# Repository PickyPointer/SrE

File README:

SrE Readme
git remote add origin https://github.com/PickyPointer/SrE.git
git push origin master
git pull origin master

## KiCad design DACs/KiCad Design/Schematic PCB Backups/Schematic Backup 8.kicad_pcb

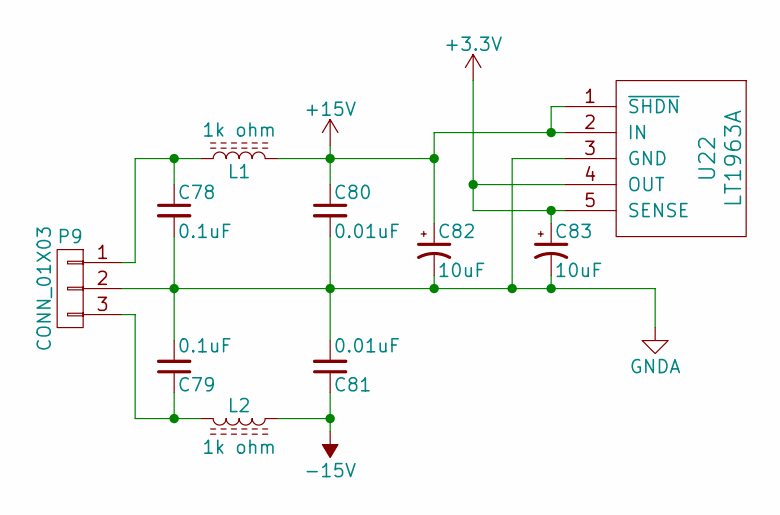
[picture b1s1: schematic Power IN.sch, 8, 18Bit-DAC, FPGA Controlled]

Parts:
C78, C79: 0.1uF; C_0805_HandSoldering
C80, C81: 0.01uF; C_0805_HandSoldering
C82, C83: 10uF; CP_Tantalum_Case-A_EIA-3216-18_Hand
L1, L2: 1k ohm; C_1812_HandSoldering
P9: CONN_01X03; PINHEAD1-3
U22: LT1963A; TO-220-5_Pentawatt_Multiwatt-5_Vertical_StaggeredType1

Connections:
+3V3: C83.1, U22.4 (OUT), U22.5 (SENSE); also elsewhere on the board
+15V: C80.1, C82.1, L1.2, U22.1 (~SHDN~), U22.2 (IN); also elsewhere on the board
-15V: C81.1, L2.2; also elsewhere on the board
GNDA: C78.2, C79.2, C80.2, C81.2, C82.2, C83.2, P9.2, U22.3 (GND); also elsewhere on the board
unnamed: C78.1, L1.1, P9.1
unnamed: C79.1, L2.1, P9.3

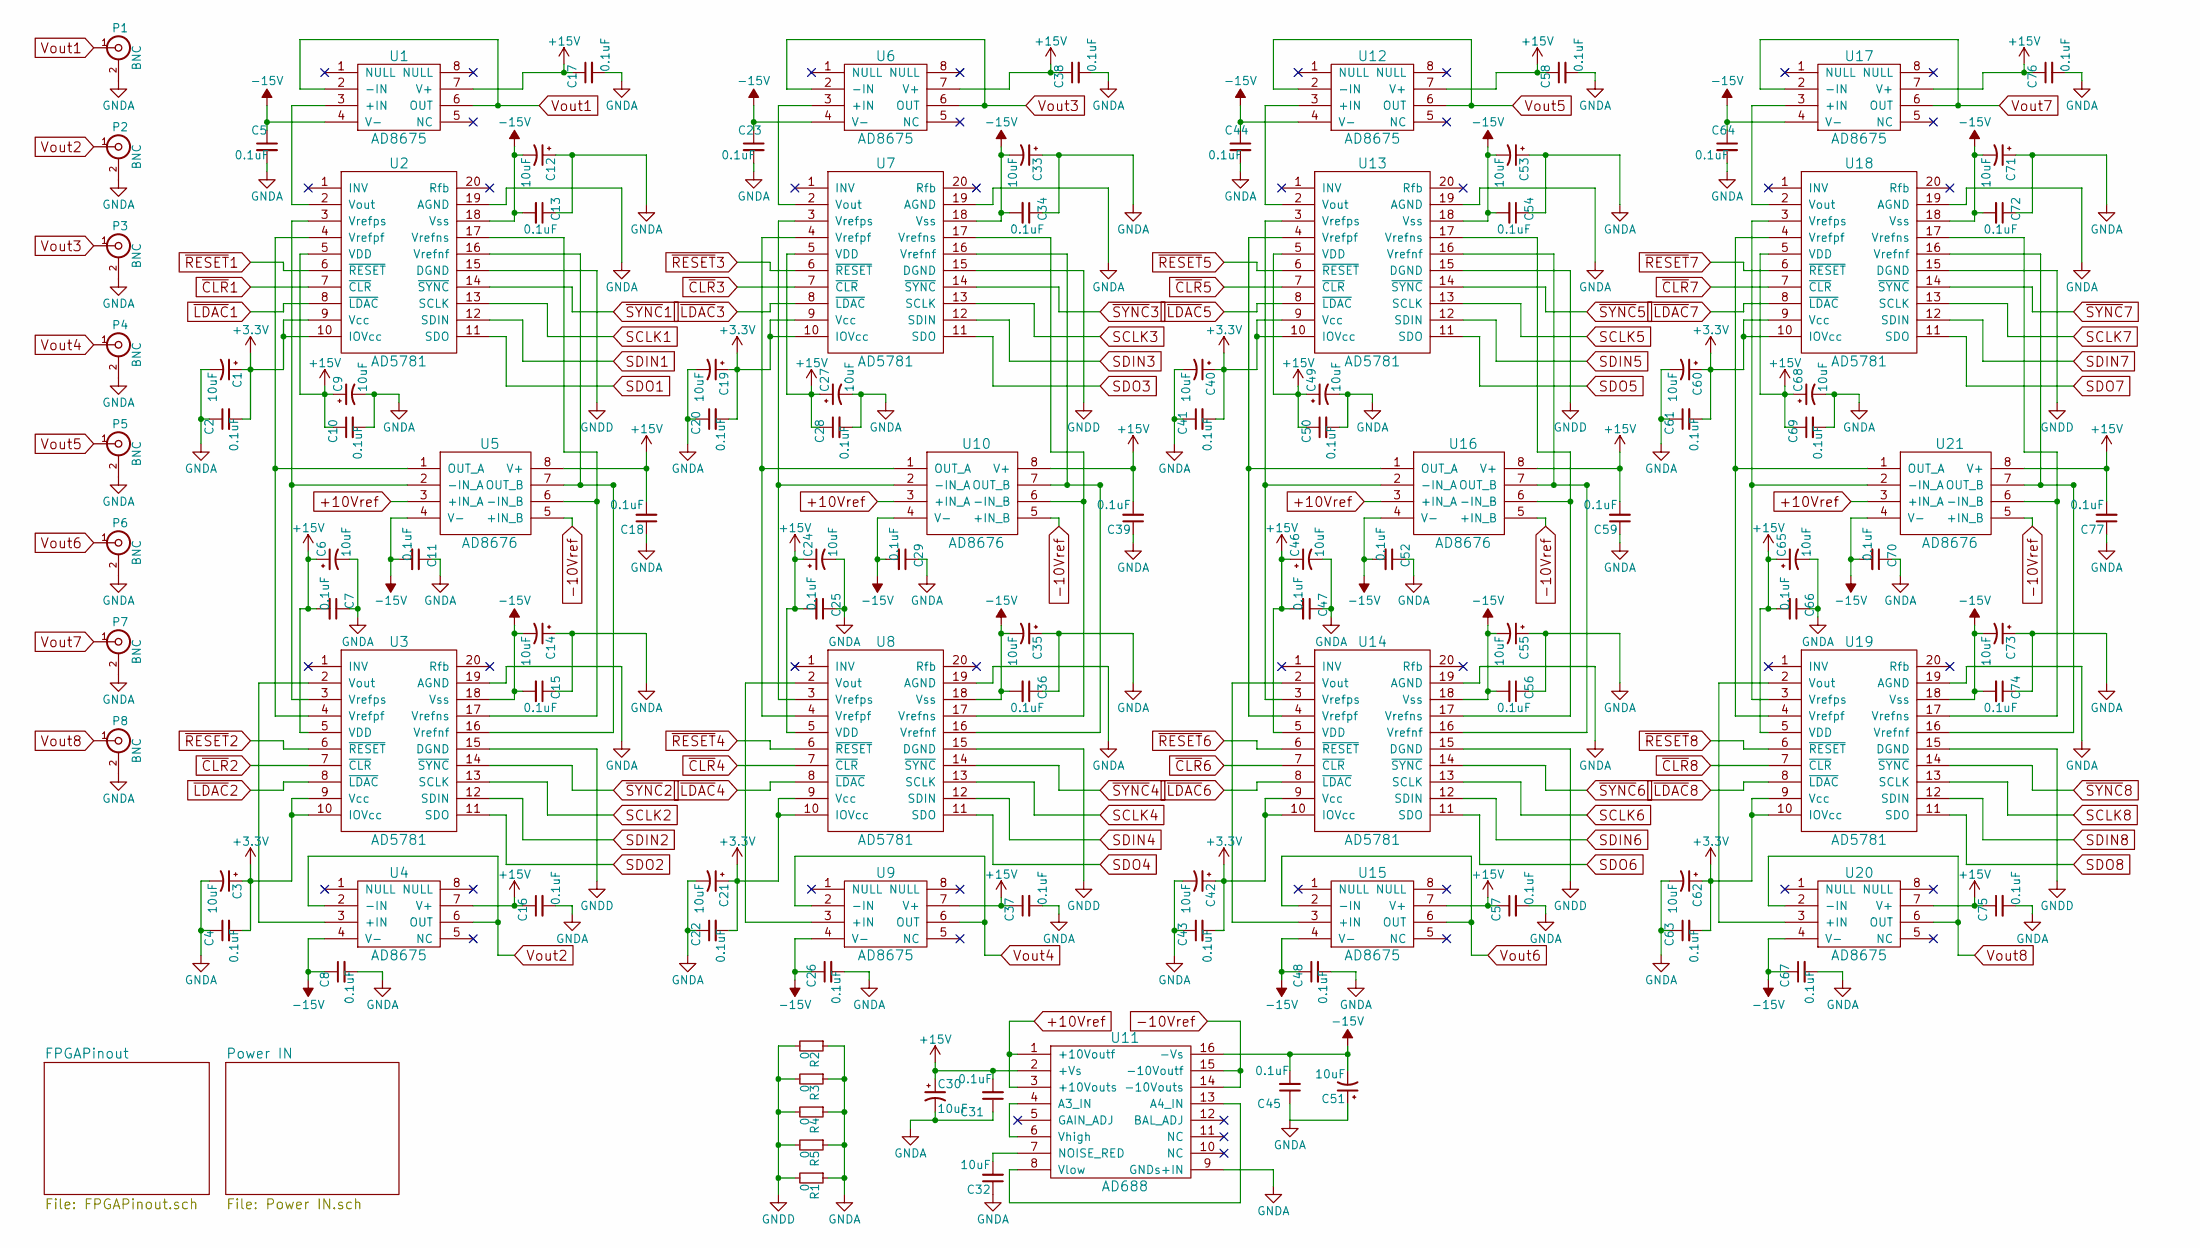
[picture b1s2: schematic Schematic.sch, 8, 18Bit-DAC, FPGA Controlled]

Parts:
C1, C3, C6, C9, C12, C14, C19, C21, C24, C27, C30, C33, C35, C40, C42, C46, C49, C51, C53, C55, C60, C62, C65, C68, C71, C73: 10uF; CP_Tantalum_Case-A_EIA-3216-18_Hand
C2, C4, C5, C7, C8, C10, C11, C13, C15, C16, C17, C18, C20, C22, C23, C25, C26, C28, C29, C31, C34, C36, C37, C38, C39, C41, C43, C44, C45, C47, C48, C50, C52, C54, C56, C57, C58, C59, C61, C63, C64, C66, C67, C69, C70, C72, C74, C75, C76, C77: 0.1uF; C_0805_HandSoldering
C32: 10uF; C_Disc_D3.4mm_W2.1mm_P2.50mm
P1, P2, P3, P4, P5, P6, P7, P8: BNC; BNC_Socket_TYCO-AMP_LargePads
R1, R2, R3, R4, R5: 0; R_0805_HandSoldering
U1, U4, U6, U9, U12, U15, U17, U20: AD8675; AD8675ARZ
U2, U3, U7, U8, U13, U14, U18, U19: AD5781; AD5781ARUZ
U5, U10, U16, U21: AD8676; AD8676ARZ
U11: AD688; AD688ARWZ

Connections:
+3V3: C1.1, C2.2, C3.1, C4.2, C19.1, C20.2, C21.1, C22.2, C40.1, C41.2, C42.1, C43.2, C60.1, C61.2, C62.1, C63.2, U2.9 (Vcc), U2.10 (IOVcc), U3.9 (Vcc), U3.10 (IOVcc), U7.9 (Vcc), U7.10 (IOVcc), U8.9 (Vcc), U8.10 (IOVcc), U13.9 (Vcc), U13.10 (IOVcc), U14.9 (Vcc), U14.10 (IOVcc), U18.9 (Vcc), U18.10 (IOVcc), U19.9 (Vcc), U19.10 (IOVcc); also elsewhere on the board
+10Vref: U5.3 (+IN_A), U10.3 (+IN_A), U11.1 (+10Voutf), U11.3 (+10Vouts), U16.3 (+IN_A), U21.3 (+IN_A)
+15V: C6.1, C7.2, C9.1, C10.1, C16.1, C17.1, C18.2, C24.1, C25.2, C27.1, C28.1, C30.1, C31.2, C37.1, C38.1, C39.2, C46.1, C47.2, C49.1, C50.1, C57.1, C58.1, C59.2, C65.1, C66.2, C68.1, C69.1, C75.1, C76.1, C77.2, U1.7 (V+), U2.5 (VDD), U3.5 (VDD), U4.7 (V+), U5.8 (V+), U6.7 (V+), U7.5 (VDD), U8.5 (VDD), U9.7 (V+), U10.8 (V+), U11.2 (+Vs), U12.7 (V+), U13.5 (VDD), U14.5 (VDD), U15.7 (V+), U16.8 (V+), U17.7 (V+), U18.5 (VDD), U19.5 (VDD), U20.7 (V+), U21.8 (V+); also elsewhere on the board
-10Vref: U5.5 (+IN_B), U10.5 (+IN_B), U11.14 (-10Vouts), U11.15 (-10Voutf), U16.5 (+IN_B), U21.5 (+IN_B)
-15V: C5.1, C8.1, C11.2, C12.2, C13.2, C14.2, C15.2, C23.1, C26.1, C29.2, C33.2, C34.2, C35.2, C36.2, C44.1, C45.2, C48.1, C51.2, C52.2, C53.2, C54.2, C55.2, C56.2, C64.1, C67.1, C70.2, C71.2, C72.2, C73.2, C74.2, U1.4 (V-), U2.18 (Vss), U3.18 (Vss), U4.4 (V-), U5.4 (V-), U6.4 (V-), U7.18 (Vss), U8.18 (Vss), U9.4 (V-), U10.4 (V-), U11.16 (-Vs), U12.4 (V-), U13.18 (Vss), U14.18 (Vss), U15.4 (V-), U16.4 (V-), U17.4 (V-), U18.18 (Vss), U19.18 (Vss), U20.4 (V-), U21.4 (V-); also elsewhere on the board
GNDA: C1.2, C2.1, C3.2, C4.1, C5.2, C6.2, C7.1, C8.2, C9.2, C10.2, C11.1, C12.1, C13.1, C14.1, C15.1, C16.2, C17.2, C18.1, C19.2, C20.1, C21.2, C22.1, C23.2, C24.2, C25.1, C26.2, C27.2, C28.2, C29.1, C30.2, C31.1, C32.1, C33.1, C34.1, C35.1, C36.1, C37.2, C38.2, C39.1, C40.2, C41.1, C42.2, C43.1, C44.2, C45.1, C46.2, C47.1, C48.2, C49.2, C50.2, C51.1, C52.1, C53.1, C54.1, C55.1, C56.1, C57.2, C58.2, C59.1, C60.2, C61.1, C62.2, C63.1, C64.2, C65.2, C66.1, C67.2, C68.2, C69.2, C70.1, C71.1, C72.1, C73.1, C74.1, C75.2, C76.2, C77.1, P1.2 (Ext), P2.2 (Ext), P3.2 (Ext), P4.2 (Ext), P5.2 (Ext), P6.2 (Ext), P7.2 (Ext), P8.2 (Ext), R1.1, R2.1, R3.1, R4.1, R5.1, U2.19 (AGND), U3.19 (AGND), U7.19 (AGND), U8.19 (AGND), U11.9 (GNDs+IN), U13.19 (AGND), U14.19 (AGND), U18.19 (AGND), U19.19 (AGND); also elsewhere on the board
GNDD: R1.2, R2.2, R3.2, R4.2, R5.2, U2.15 (DGND), U3.15 (DGND), U7.15 (DGND), U8.15 (DGND), U13.15 (DGND), U14.15 (DGND), U18.15 (DGND), U19.15 (DGND); also elsewhere on the board
unnamed: C32.2, U11.7 (NOISE_RED)
unnamed: U1.3 (+IN), U2.2 (Vout)
unnamed: U2.3 (Vrefps), U3.3 (Vrefps), U5.2 (-IN_A)
unnamed: U2.4 (Vrefpf), U3.4 (Vrefpf), U5.1 (OUT_A)
unnamed: U2.16 (Vrefnf), U3.16 (Vrefnf), U5.7 (OUT_B)
unnamed: U2.17 (Vrefns), U3.17 (Vrefns), U5.6 (-IN_B)
unnamed: U3.2 (Vout), U4.3 (+IN)
unnamed: U6.3 (+IN), U7.2 (Vout)
unnamed: U8.2 (Vout), U9.3 (+IN)
unnamed: U7.4 (Vrefpf), U8.4 (Vrefpf), U10.1 (OUT_A)
unnamed: U7.3 (Vrefps), U8.3 (Vrefps), U10.2 (-IN_A)
unnamed: U7.17 (Vrefns), U8.17 (Vrefns), U10.6 (-IN_B)
unnamed: U7.16 (Vrefnf), U8.16 (Vrefnf), U10.7 (OUT_B)
unnamed: U11.4 (A3_IN), U11.6 (Vhigh)
unnamed: U11.8 (Vlow), U11.13 (A4_IN)
unnamed: U12.3 (+IN), U13.2 (Vout)
unnamed: U13.3 (Vrefps), U14.3 (Vrefps), U16.2 (-IN_A)
unnamed: U13.4 (Vrefpf), U14.4 (Vrefpf), U16.1 (OUT_A)
unnamed: U13.16 (Vrefnf), U14.16 (Vrefnf), U16.7 (OUT_B)
unnamed: U13.17 (Vrefns), U14.17 (Vrefns), U16.6 (-IN_B)
unnamed: U14.2 (Vout), U15.3 (+IN)
unnamed: U17.3 (+IN), U18.2 (Vout)
unnamed: U18.3 (Vrefps), U19.3 (Vrefps), U21.2 (-IN_A)
unnamed: U18.4 (Vrefpf), U19.4 (Vrefpf), U21.1 (OUT_A)
unnamed: U18.16 (Vrefnf), U19.16 (Vrefnf), U21.7 (OUT_B)
unnamed: U18.17 (Vrefns), U19.17 (Vrefns), U21.6 (-IN_B)
unnamed: U19.2 (Vout), U20.3 (+IN)
SCLK1: U2.13 (SCLK); also elsewhere on the board
SCLK2: U3.13 (SCLK); also elsewhere on the board
SCLK3: U7.13 (SCLK); also elsewhere on the board
SCLK4: U8.13 (SCLK); also elsewhere on the board
SCLK5: U13.13 (SCLK); also elsewhere on the board
SCLK6: U14.13 (SCLK); also elsewhere on the board
SCLK7: U18.13 (SCLK); also elsewhere on the board
SCLK8: U19.13 (SCLK); also elsewhere on the board
SDIN1: U2.12 (SDIN); also elsewhere on the board
SDIN2: U3.12 (SDIN); also elsewhere on the board
SDIN3: U7.12 (SDIN); also elsewhere on the board
SDIN4: U8.12 (SDIN); also elsewhere on the board
SDIN5: U13.12 (SDIN); also elsewhere on the board
SDIN6: U14.12 (SDIN); also elsewhere on the board
SDIN7: U18.12 (SDIN); also elsewhere on the board
SDIN8: U19.12 (SDIN); also elsewhere on the board
SDO1: U2.11 (SDO); also elsewhere on the board
SDO2: U3.11 (SDO); also elsewhere on the board
SDO3: U7.11 (SDO); also elsewhere on the board
SDO4: U8.11 (SDO); also elsewhere on the board
SDO5: U13.11 (SDO); also elsewhere on the board
SDO6: U14.11 (SDO); also elsewhere on the board
SDO7: U18.11 (SDO); also elsewhere on the board
SDO8: U19.11 (SDO); also elsewhere on the board
Vout1: P1.1 (In), U1.2 (-IN), U1.6 (OUT)
Vout2: P2.1 (In), U4.2 (-IN), U4.6 (OUT)
Vout3: P3.1 (In), U6.2 (-IN), U6.6 (OUT)
Vout4: P4.1 (In), U9.2 (-IN), U9.6 (OUT)
Vout5: P5.1 (In), U12.2 (-IN), U12.6 (OUT)
Vout6: P6.1 (In), U15.2 (-IN), U15.6 (OUT)
Vout7: P7.1 (In), U17.2 (-IN), U17.6 (OUT)
Vout8: P8.1 (In), U20.2 (-IN), U20.6 (OUT)
~CLR~1: U2.7 (~CLR~); also elsewhere on the board
~CLR~2: U3.7 (~CLR~); also elsewhere on the board
~CLR~3: U7.7 (~CLR~); also elsewhere on the board
~CLR~4: U8.7 (~CLR~); also elsewhere on the board
~CLR~5: U13.7 (~CLR~); also elsewhere on the board
~CLR~6: U14.7 (~CLR~); also elsewhere on the board
~CLR~7: U18.7 (~CLR~); also elsewhere on the board
~CLR~8: U19.7 (~CLR~); also elsewhere on the board
~LDAC~1: U2.8 (~LDAC~); also elsewhere on the board
~LDAC~2: U3.8 (~LDAC~); also elsewhere on the board
~LDAC~3: U7.8 (~LDAC~); also elsewhere on the board
~LDAC~4: U8.8 (~LDAC~); also elsewhere on the board
~LDAC~5: U13.8 (~LDAC~); also elsewhere on the board
~LDAC~6: U14.8 (~LDAC~); also elsewhere on the board
~LDAC~7: U18.8 (~LDAC~); also elsewhere on the board
~LDAC~8: U19.8 (~LDAC~); also elsewhere on the board
~RESET~1: U2.6 (~RESET~); also elsewhere on the board
~RESET~2: U3.6 (~RESET~); also elsewhere on the board
~RESET~3: U7.6 (~RESET~); also elsewhere on the board
~RESET~4: U8.6 (~RESET~); also elsewhere on the board
~RESET~5: U13.6 (~RESET~); also elsewhere on the board
~RESET~6: U14.6 (~RESET~); also elsewhere on the board
~RESET~7: U18.6 (~RESET~); also elsewhere on the board
~RESET~8: U19.6 (~RESET~); also elsewhere on the board
~SYNC~1: U2.14 (~SYNC~); also elsewhere on the board
~SYNC~2: U3.14 (~SYNC~); also elsewhere on the board
~SYNC~3: U7.14 (~SYNC~); also elsewhere on the board
~SYNC~4: U8.14 (~SYNC~); also elsewhere on the board
~SYNC~5: U13.14 (~SYNC~); also elsewhere on the board
~SYNC~6: U14.14 (~SYNC~); also elsewhere on the board
~SYNC~7: U18.14 (~SYNC~); also elsewhere on the board
~SYNC~8: U19.14 (~SYNC~); also elsewhere on the board

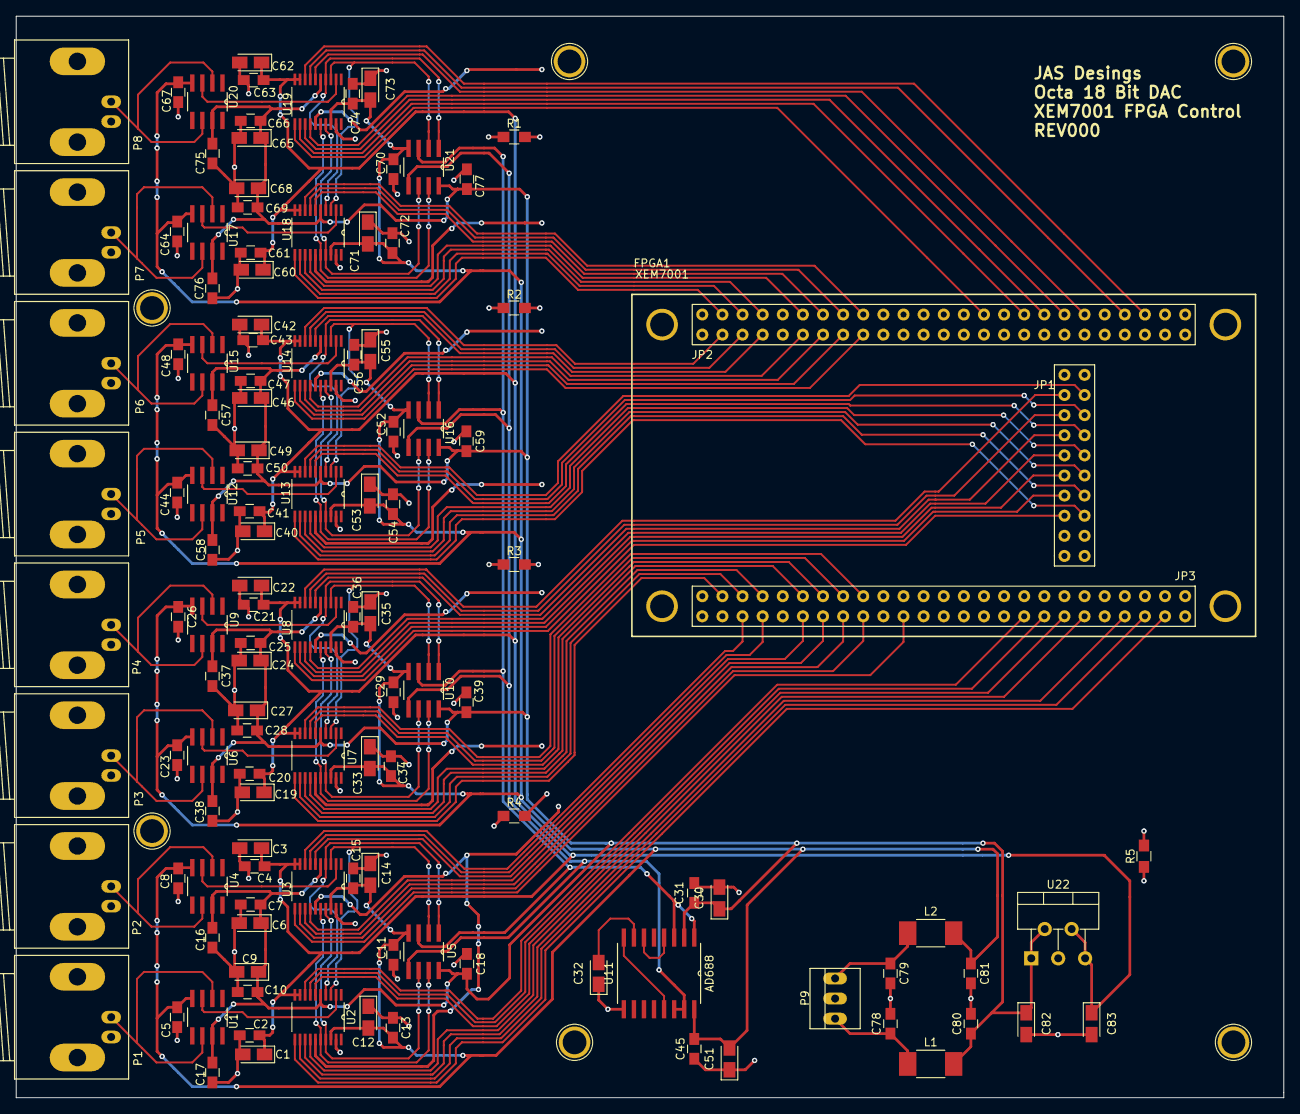
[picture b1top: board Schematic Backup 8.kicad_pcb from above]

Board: 2 copper layers, 160.0 x 136.5 mm, 122 parts (0 on the bottom side), 100 nets.

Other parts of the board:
FPGA1: XEM7001

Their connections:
GNDD: FPGA1.GNDi; also elsewhere on the board
SCLK1: FPGA1.C9; also elsewhere on the board
SCLK2: FPGA1.E15; also elsewhere on the board
SCLK3: FPGA1.H13; also elsewhere on the board
SCLK4: FPGA1.C1; also elsewhere on the board
SCLK5: FPGA1.C2; also elsewhere on the board
SCLK6: FPGA1.P8; also elsewhere on the board
SCLK7: FPGA1.T9; also elsewhere on the board
SCLK8: FPGA1.M2; also elsewhere on the board
SDIN1: FPGA1.D10; also elsewhere on the board
SDIN2: FPGA1.D14; also elsewhere on the board
SDIN3: FPGA1.F15; also elsewhere on the board
SDIN4: FPGA1.B1; also elsewhere on the board
SDIN5: FPGA1.B2; also elsewhere on the board
SDIN6: FPGA1.N6; also elsewhere on the board
SDIN7: FPGA1.T7; also elsewhere on the board
SDIN8: FPGA1.M4; also elsewhere on the board
SDO1: FPGA1.D9; also elsewhere on the board
SDO2: FPGA1.D15; also elsewhere on the board
SDO3: FPGA1.E12; also elsewhere on the board
SDO4: FPGA1.A2; also elsewhere on the board
SDO5: FPGA1.A3; also elsewhere on the board
SDO6: FPGA1.T4; also elsewhere on the board
SDO7: FPGA1.T8; also elsewhere on the board
SDO8: FPGA1.N2; also elsewhere on the board
~CLR~1: FPGA1.A12; also elsewhere on the board
~CLR~2: FPGA1.H16; also elsewhere on the board
~CLR~3: FPGA1.E16; also elsewhere on the board
~CLR~4: FPGA1.G1; also elsewhere on the board
~CLR~5: FPGA1.G2; also elsewhere on the board
~CLR~6: FPGA1.R8; also elsewhere on the board
~CLR~7: FPGA1.P5; also elsewhere on the board
~CLR~8: FPGA1.K2; also elsewhere on the board
~LDAC~1: FPGA1.F13; also elsewhere on the board
~LDAC~2: FPGA1.G14; also elsewhere on the board
~LDAC~3: FPGA1.D16; also elsewhere on the board
~LDAC~4: FPGA1.H1; also elsewhere on the board
~LDAC~5: FPGA1.H2; also elsewhere on the board
~LDAC~6: FPGA1.T10; also elsewhere on the board
~LDAC~7: FPGA1.P4; also elsewhere on the board
~LDAC~8: FPGA1.J1; also elsewhere on the board
~RESET~1: FPGA1.C11; also elsewhere on the board
~RESET~2: FPGA1.G16; also elsewhere on the board
~RESET~3: FPGA1.G15; also elsewhere on the board
~RESET~4: FPGA1.F2; also elsewhere on the board
~RESET~5: FPGA1.E1; also elsewhere on the board
~RESET~6: FPGA1.R7; also elsewhere on the board
~RESET~7: FPGA1.R5; also elsewhere on the board
~RESET~8: FPGA1.L2; also elsewhere on the board
~SYNC~1: FPGA1.A10; also elsewhere on the board
~SYNC~2: FPGA1.F14; also elsewhere on the board
~SYNC~3: FPGA1.H14; also elsewhere on the board
~SYNC~4: FPGA1.E2; also elsewhere on the board
~SYNC~5: FPGA1.D1; also elsewhere on the board
~SYNC~6: FPGA1.R6; also elsewhere on the board
~SYNC~7: FPGA1.T5; also elsewhere on the board
~SYNC~8: FPGA1.L3; also elsewhere on the board

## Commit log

2018-03-26 Added Felixs files
2018-03-26 Trying to push updated readme
2018-03-26 Working on guis for TTL
2018-04-14 Working test TTL from Felix
2018-08-05 Adding labrad-tools
2018-08-05 updated picoscope server for 5000 series
2018-08-06 added new sequences
2018-08-07 Ross's changes from last night + Jacob's DAC code
2018-08-07 ross's recorder changes
2018-08-10 updated labrad_tools
2018-08-14 Updates from YeElmo setup
2018-08-14 added plotter memory leak fix from yecookiemonster
2018-08-15 got rid of recorder sequence print cancer
2018-08-15 corrected okfpga server name to yeelmo_okfpga
2018-08-15 updated ad9956_0 and ad9956_1 to reflect new udev rules
2018-08-15 Added device class and devices for serial communication with Sr1 blue current controller
2018-08-15 updated channel list for blue current controller client
2018-08-15 update to current_controller devices for interface name
2018-08-16 Serial version of ldc80xx fixed
2018-08-16 silenced current_control.py
2018-08-17 Added new sequence to recorder
2018-08-21 Got plotter up and running. Commit just in case. Now its on yecountvoncount
2018-08-21 conductor updated to work with new plot
2018-08-21 Updated to work with count von count
2018-08-22 Ross changed PMT class to have recording option
2018-08-31 added updates from when Eric was on vacation
2018-08-31 Changed Picoscope range to 1 V for better resolution with default PMT preamp settings
2018-08-31 Colin's new PMT client added
2018-08-31 Added Colin's client Icons and new PMT client
2018-08-31 removed redundant rf.py.save
2018-08-31 Set up to ignore .pyc on yebigbird
2018-08-31 added .gitignore file to ignore .pyc and .directory files
2018-09-04 added sequence to recorder.py. Added rf device cu_pulse for clean-up pulse sg382 synthesizer
2018-09-04 fixed cu_pulse.py so it will autostart
2018-09-04 added more sequences to recorder.py. added hr_demod_frequency_cleanup.py parameter to clock_fiber_aom conductor devices
2018-09-04 fixed typo in conductor/devices/clock_fiber_aom/hr_demod_frequency_cleanup.py
2018-09-11 Changed e.py to work with Ross_DAC_1 FPGA. For new DAC module
2018-09-15 added server for Ethernet-GPIB
2018-09-18 Changed DAC e channel names. Added new sequences to recorder pmt list.
2018-09-18 Changed lock settings to use second integrator
2018-09-19 Added new VXI11 blues control. Still needs to be debugged before we can run the server
2018-09-22 Updated current controller for VXI11. Server works but client doesnt. Need to ask ross.
2018-09-26 added cleanup pulse sequences to recorder.py
2018-09-26 more recorder.py maintainance
2018-09-26 added client_tools/connection2.py to allow clients to talk to Sr2 labrad manager
2018-09-26 added client for 813 wavemeter on Sr 2 labrad network
2018-10-31 Added ramsey sequency to PMT recorder list
